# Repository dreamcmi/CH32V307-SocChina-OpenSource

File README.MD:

# RISC-V MCU 基于CH32V307的智能家居中控系统

```shell
软件:
CH32V307VCT6-SOCCHINA  主控源码
CH571F-Hall 门窗传感器源码
CH582F-Receiver-uart 中心节点转发器源码
硬件:
CH582F_Hall_Switch-v1.0.0 节点硬件(Kicad6.0)
```
# LICENSE: GPL-3.0

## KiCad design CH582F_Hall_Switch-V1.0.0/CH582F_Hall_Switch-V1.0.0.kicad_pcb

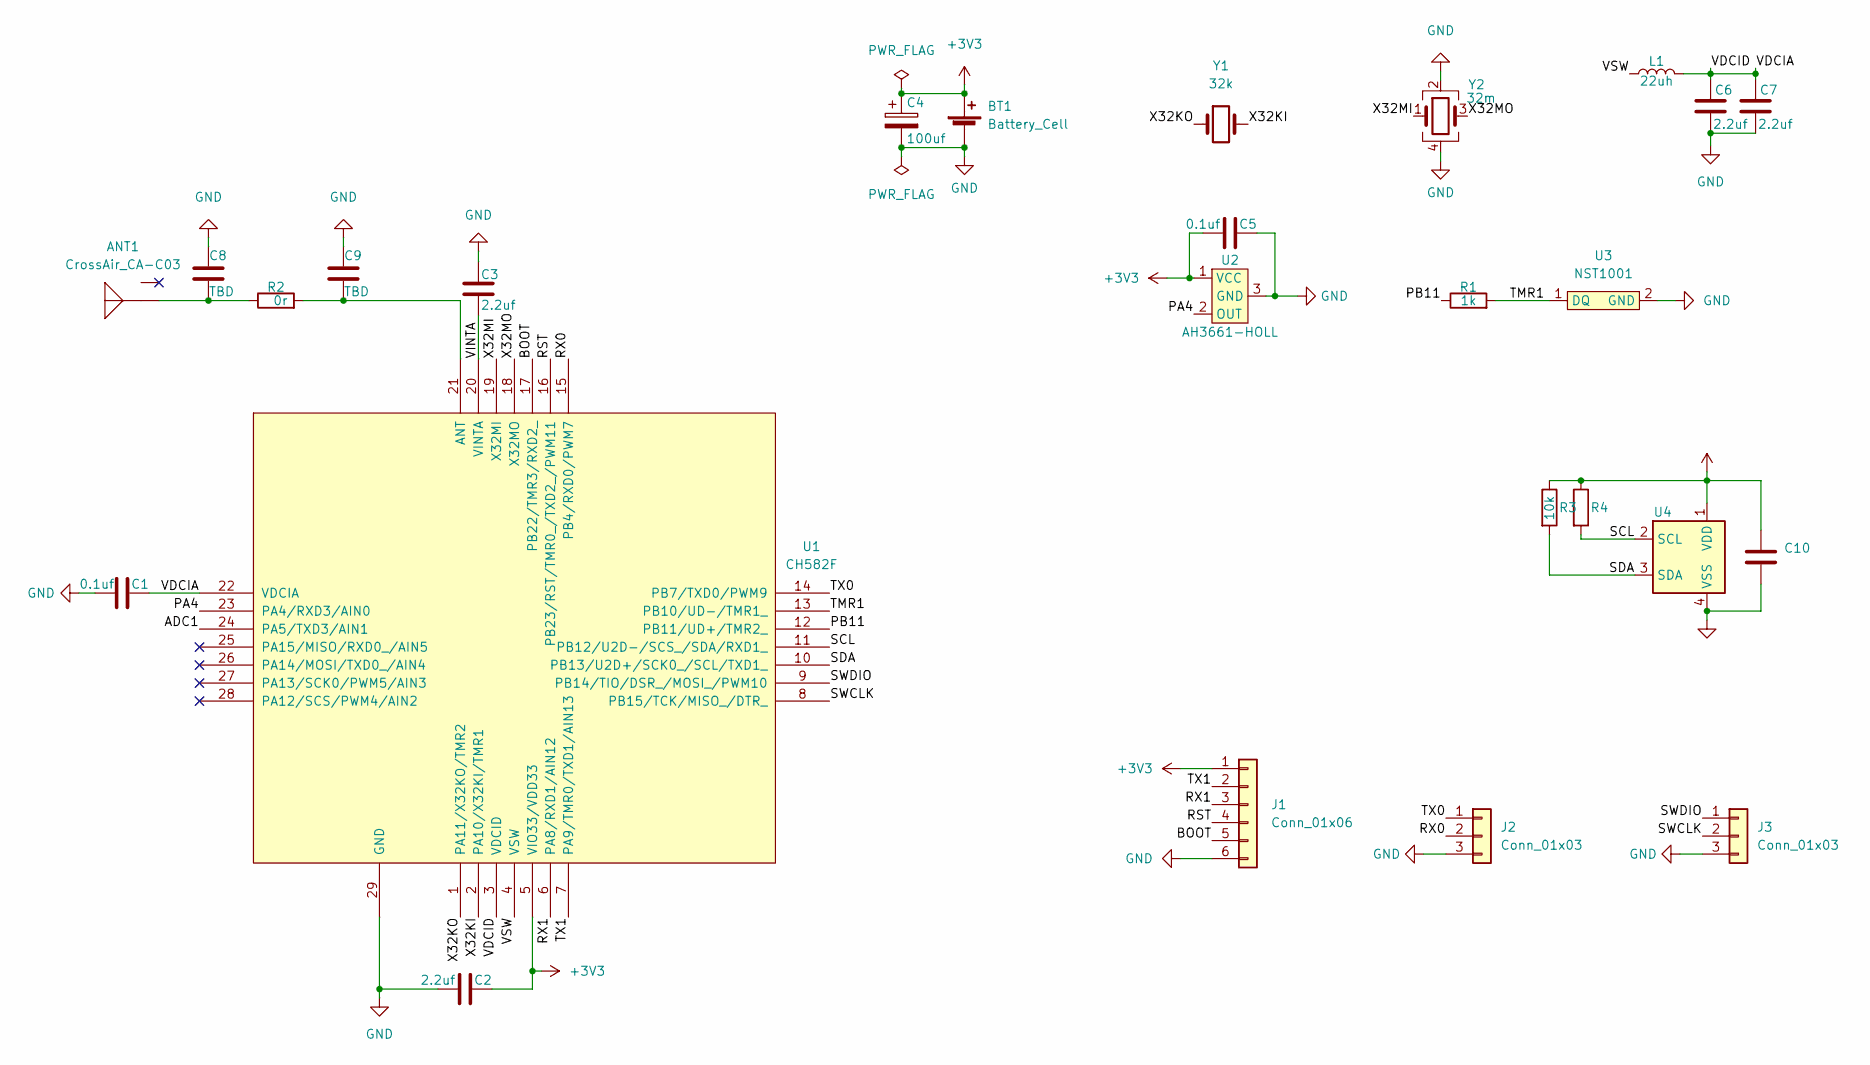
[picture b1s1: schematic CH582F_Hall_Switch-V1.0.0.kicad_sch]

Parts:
ANT1: CrossAir_CA-C03; CA-C03
BT1: Battery_Cell; BAT-TH_CR2032-BS-6-1
C1, C5: 0.1uf; C_0603_1608Metric
C2, C3, C6, C7: 2.2uf; C_0603_1608Metric
C4: 100uf; CP_EIA-3528-21_Kemet-B
C8, C9: TBD
C10: (no value)
J1: Conn_01x06
J2, J3: Conn_01x03
L1: 22uh; L_0805_2012Metric
R1: 1k; R_0603_1608Metric
R2: 0r
R3: 10k
R4: (no value)
U1: CH582F; QFN-28-1EP_4x4mm_P0.4mm_EP2.3x2.3mm
U2: AH3661-HOLL; SOT-23
U3: NST1001; DFN-2L_L1.6-W0.8-P0.85-L
U4: (no value)
Y1: 32k; Crystal_SMD_3215-2Pin_3.2x1.5mm
Y2: 32m; Crystal_SMD_3225-4Pin_3.2x2.5mm

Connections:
/ADC1: U1.24 (PA5/TXD3/AIN1)
/BOOT: J1.5, U1.17 (PB22/TMR3/RXD2_)
/PA4: U1.23 (PA4/RXD3/AIN0), U2.2 (OUT)
/PB11: R1.1, U1.12 (PB11/UD+/TMR2_)
/RST: J1.4, U1.16 (PB23/RST/TMR0_/TXD2_/PWM11)
/RX0: J2.2, U1.15 (PB4/RXD0/PWM7)
/RX1: J1.3, U1.6 (PA8/RXD1/AIN12)
/SCL: R4.2, U1.11 (PB12/U2D-/SCS_/SDA/RXD1_), U4.2 (SCL)
/SDA: R3.2, U1.10 (PB13/U2D+/SCK0_/SCL/TXD1_), U4.3 (SDA)
/SWCLK: J3.2, U1.8 (PB15/TCK/MISO_/DTR_)
/SWDIO: J3.1, U1.9 (PB14/TIO/DSR_/MOSI_/PWM10)
/TMR1: R1.2, U1.13 (PB10/UD-/TMR1_), U3.1 (DQ)
/TX0: J2.1, U1.14 (PB7/TXD0/PWM9)
/TX1: J1.2, U1.7 (PA9/TMR0/TXD1/AIN13)
/VDCIA: C1.2, C6.1, C7.1, L1.2, U1.3 (VDCID), U1.22 (VDCIA)
/VINTA: C3.2, U1.20 (VINTA)
/VSW: L1.1, U1.4 (VSW)
/X32KI: U1.2 (PA10/X32KI/TMR1), Y1.2
/X32KO: U1.1 (PA11/X32KO/TMR2), Y1.1
/X32MI: U1.19 (X32MI), Y2.1
/X32MO: U1.18 (X32MO), Y2.3
unnamed: ANT1.1 (ANT), C8.2, R2.1
unnamed: C9.2, R2.2, U1.21 (ANT)

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
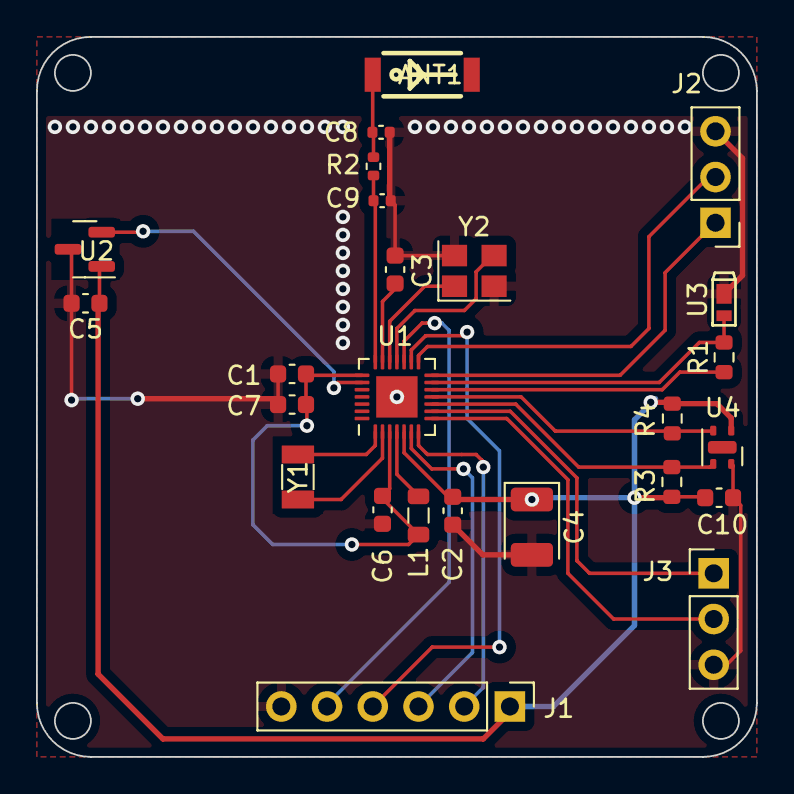
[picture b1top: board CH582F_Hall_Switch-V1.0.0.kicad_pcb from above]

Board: 2 copper layers, 40.0 x 40.0 mm, 26 parts (1 on the bottom side), 24 nets.

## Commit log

2022-07-14 init
